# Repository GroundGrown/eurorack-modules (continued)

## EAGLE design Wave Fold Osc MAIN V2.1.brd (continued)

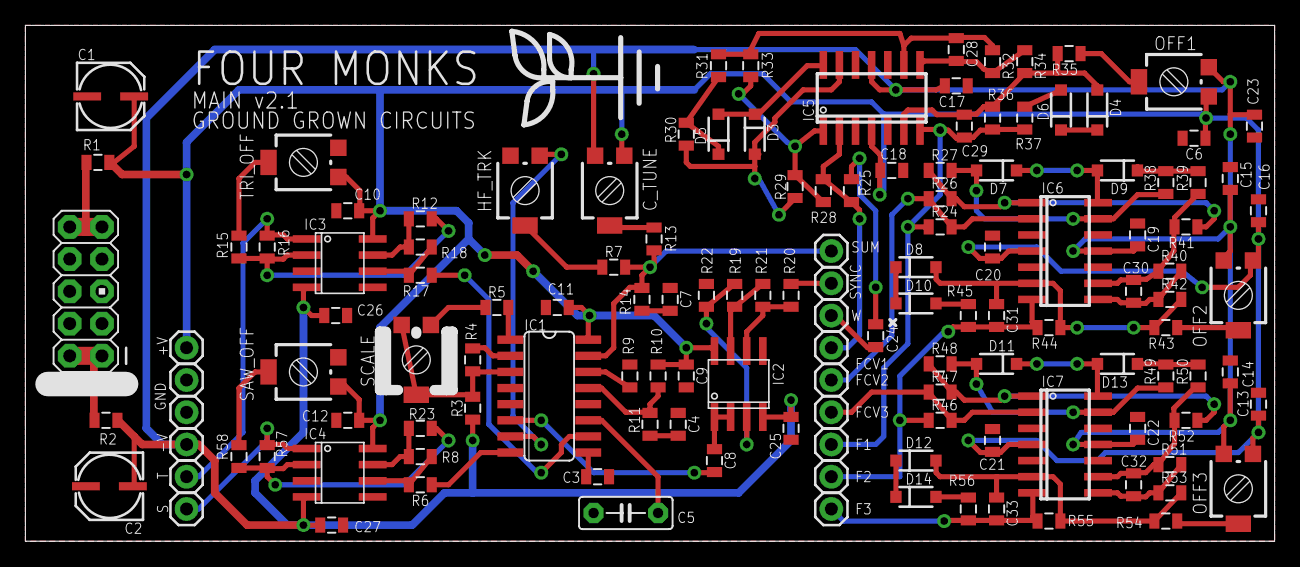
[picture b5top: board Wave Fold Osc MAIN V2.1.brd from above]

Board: 2 copper layers, 98.4 x 40.6 mm, 135 parts (0 on the bottom side), 75 nets.

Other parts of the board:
U$1: LOGO_MED
